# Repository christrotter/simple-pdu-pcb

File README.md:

# simple-pdu-pcb
This PCB allows you to wire up eight `DC-005` horizontal barrel connectors onto a single PCB, with an optional power LED.    Silkscreen note which resistors you need for a ~3.2v green led.... didn't mention what led specs you needed.  Hum.  Anyways.

# Details
- Supply whatever voltage you need - top layer is a full copper pour for power plane, bottom layer is a full copper pour for ground plane.
- 25x170mm (_10mm gaps between barrel connectors_)
- extra breakouts for ground and power
- led + resistor through-hole mounts
- 4x M3 plated/via'd mount holes (_middle two centers are 40mm apart, outer two centers are 5mm from edge, outer to middle centers are 60mm apart_)
- 3-pin 2.54mm-spaced terminal block to connect source (_what I had on hand - 2-pin will work fine_)
- DC-005 connectors are 3.8?mm off the end of the board for flush-mounting in a 3D-printed enclosure.

# Why
As part of my long-standing 'do something about the desk wiring already' project, we take the first step: DC wiring

I have two ATX power supplies mounted to the underside of the desk right now and it's dubiously wired at best.
To remedy this, and simplify the setup, I'm moving to one PSU and some breakout boards.

Because patterns are useful, I made this pcb to work with 3.3 or 5 or 12 volts.  So I will use 3 boards - one per rail.

# Future ideas
- Having one connector type and multiple voltages is not a great design choice.
- I didn't note what kind of led needs those resistor values.
- Should have added notation on hole spacing to silkscreen.

# Schematic

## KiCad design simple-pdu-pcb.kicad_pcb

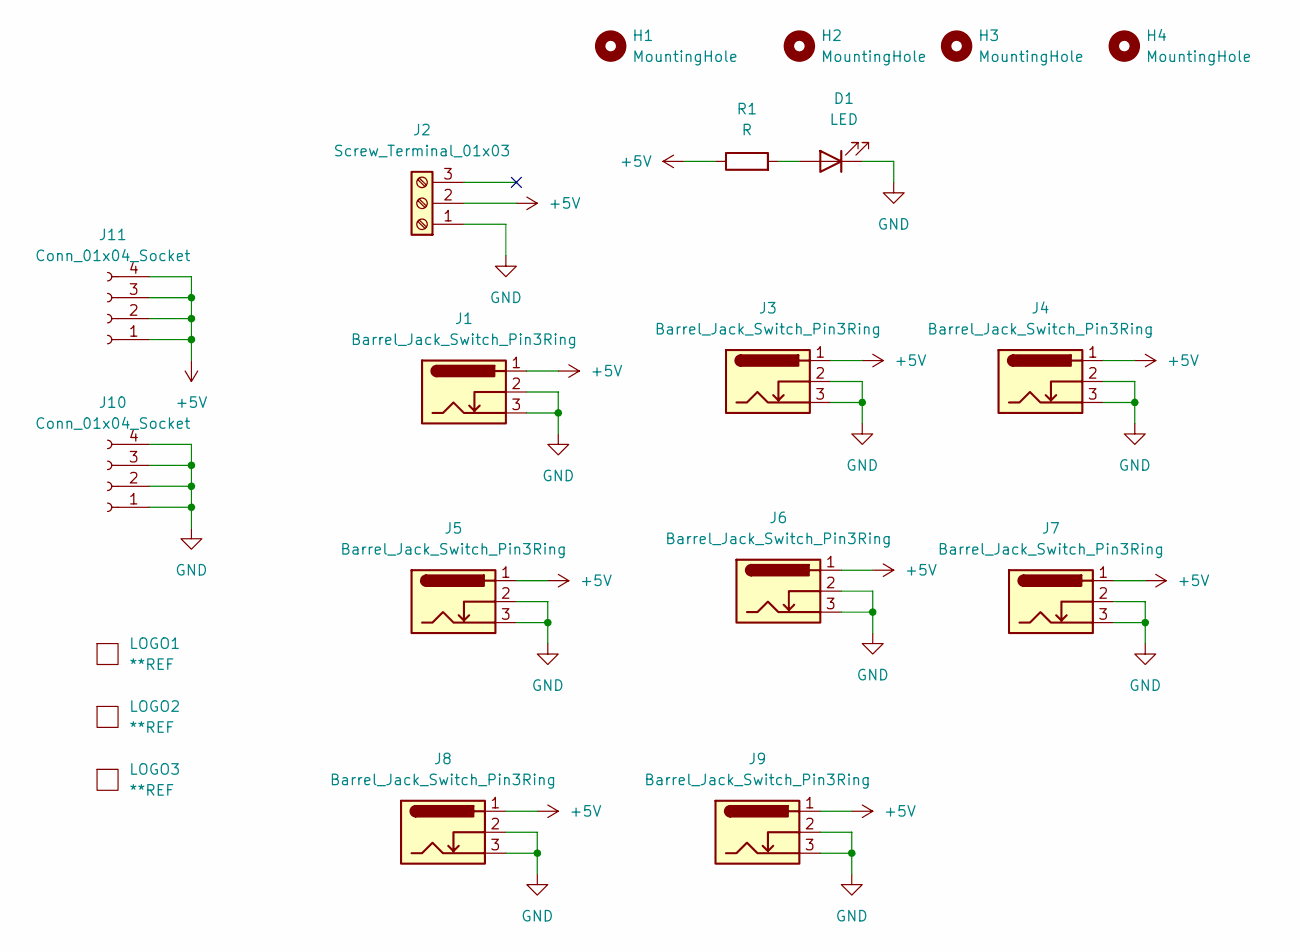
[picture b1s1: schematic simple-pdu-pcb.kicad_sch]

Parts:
D1: LED; LED_D3.0mm_Horizontal_O3.81mm_Z10.0mm
H1, H2, H3, H4: MountingHole; MountingHole_3.2mm_M3_Pad_Via
J1, J3, J4, J5, J6, J7, J8, J9: Barrel_Jack_Switch_Pin3Ring; BarrelJack_Horizontal
J2: Screw_Terminal_01x03; TerminalBlock_Xinya_XY308-2.54-3P_1x03_P2.54mm_Horizontal
J10, J11: Conn_01x04_Socket; PinSocket_1x04_P2.54mm_Vertical
LOGO1, LOGO2: **REF; awesome-logo
LOGO3: **REF; simple-pdu-pcb-qr-10mm
R1: R; R_Axial_DIN0207_L6.3mm_D2.5mm_P10.16mm_Horizontal

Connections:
+5V: J1.1, J2.2, J3.1, J4.1, J5.1, J6.1, J7.1, J8.1, J9.1, J11.1, J11.2, J11.3, J11.4, R1.1
GND: D1.1 (K), J1.2, J1.3, J2.1, J3.2, J3.3, J4.2, J4.3, J5.2, J5.3, J6.2, J6.3, J7.2, J7.3, J8.2, J8.3, J9.2, J9.3, J10.1, J10.2, J10.3, J10.4
unnamed: D1.2 (A), R1.2

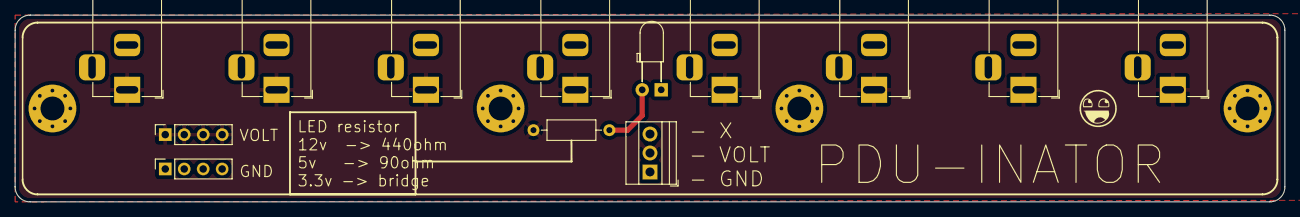
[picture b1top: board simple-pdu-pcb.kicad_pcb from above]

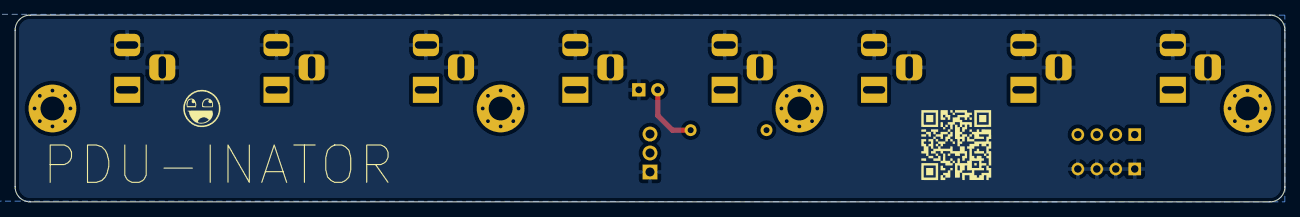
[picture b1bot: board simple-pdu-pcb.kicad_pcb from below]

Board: 2 copper layers, 170.0 x 25.0 mm, 20 parts (2 on the bottom side), 3 nets.

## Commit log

2024-12-11 first order placed
2024-12-11 adding readme and images
